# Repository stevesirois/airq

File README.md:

# AirQ

An indoor air-quality monitor built around an ESP32-C6 and a [Sensirion SEN66](https://sensirion.com/products/catalog/SEN66) sensor, running [ESPHome](https://esphome.io/) and reporting into [Home Assistant](https://www.home-assistant.io/) that will cost you around 125$ (CAD).

The SEN66 is an all-in-one environmental sensor that measures:

- **CO₂** concentration
- **PM1.0 / PM2.5 / PM4.0 / PM10** particulate matter
- **Temperature** and **relative humidity**
- **VOC index** and **NOx index**

These values are published to Home Assistant as individual sensor entities over Wi-Fi, using ESPHome's native API.

## Project structure

| Path                                 | Purpose                                                         |
| ------------------------------------ | --------------------------------------------------------------- |
| `airq.yaml`                          | ESPHome config for the **WaveShare ESP32-C6-Zero / mini** board |
| `airqx.yaml`                         | ESPHome config for the **Seeed Studio XIAO ESP32-C6** board     |
| `airQ (PCB)/`                        | KiCad carrier/breakout PCB (ESP32-C6 + SEN66 headers)           |
| `3D-Print/`                          | 3D-printable enclosure (body, cover, TPU gasket) + assembly     |
| `BOM.ods`, `BOM.csv`                 | Bill of materials spreadsheet                                   |
| `sensirion-datasheet-SEN6x-V1.0.pdf` | SEN66 sensor datasheet                                          |

## Hardware

- **MCU board:** either a
  - [WaveShare ESP32-C6-Zero / ESP32-C6 mini](https://www.espboards.dev/esp32/esp32-c6-zero-mini/) ([docs](https://docs.waveshare.com/ESP32-C6-Zero)), or a
  - [Seeed Studio XIAO ESP32C6](https://wiki.seeedstudio.com/xiao_esp32c6_getting_started/)
- **Sensor:** [Sensirion SEN66](https://sensirion.com/products/catalog/SEN66) (SEN6x family)
- **Carrier PCB:** a small breakout board (KiCad project in `airQ (PCB)/`) that hosts the ESP32-C6 board and the SEN66. Its headers are pin headers only — you solder the ESP32-C6 board and connect the sensor via its 6-pin cable. Manufacturable via [JLCPCB](https://jlcpcb.com/) using the files in `airQ (PCB)/production/`.
- **Enclosure:** 3D-printable body, cover, and TPU gasket (see `3D-Print/`), sized for the SEN66 with proper airflow openings (≥56 mm² inlet / ≥148 mm² outlet per Sensirion guidelines).

### Wiring (I²C)

| Board (config)                        | SCL    | SDA    |
| ------------------------------------- | ------ | ------ |
| WaveShare ESP32-C6-Zero (`airq.yaml`) | GPIO22 | GPIO21 |
| XIAO ESP32-C6 (`airqx.yaml`)          | GPIO23 | GPIO22 |

## Requirements

- **ESPHome** — see [esphome.io](https://esphome.io/) for installation. I suggest to use the executable version if you use Windows/MacOS or the AppImage if your are on Linux since this is the easiest way to use ESPHome

## Usage

1. Check the BOM.ods for all the required parts
2. Order your PCB from JLCPCB using the airQ.zip file that is ready for production
3. Depending of the controler used, short the 4 x 3 pins connectors accordingly on the PCB. The side mark "M" is for the Waveshare mini and the other side is for the Seeed XIAO (mark "X").
4. Print the enclosure
5. Configure and flash your controler using ESPHome. I put 2 yaml files that show the correct configuration for each board. The important part is the IO pin for the I²C interface vs the PCB board design
6. Assemble everything and hopefully it should work :-)

## Home Assistant dashboard for the sensor

To show the dashboard card (see picture in photo folder), install HACS (Home Assistant Community Store) and add the [Air Quality Card by KadenThomp36](https://github.com/KadenThomp36/Air-Quality-Card). The thresholds follow the WHO 2021 recommendations that this card also uses, so the recommendations on the device's display and the dashboard will stay consistent.

## Ordering / manufacturing

- **PCB:** upload the Gerber/drill files (the zip file) generated from `airQ (PCB)/production/airQ.zip` to [JLCPCB](https://jlcpcb.com/). The `production/` folder contains BOM and placement (CPL) exports for assembly.
- **Enclosure:** print the parts in `3D-Print/` (PLA body/cover, TPU for the gasket). See `3D-Print/README.md` for details.

## References

- [ESPHome](https://esphome.io/)
- [ESP32-C6-Zero — ESPBoards](https://www.espboards.dev/esp32/esp32-c6-zero-mini/)
- [ESP32-C6-Zero — WaveShare docs](https://docs.waveshare.com/ESP32-C6-Zero)
- [XIAO ESP32-C6 — ESPBoards](https://www.espboards.dev/esp32/xiao-esp32c6/)
- [XIAO ESP32-C6 — Seeed Studio wiki](https://wiki.seeedstudio.com/xiao_esp32c6_getting_started/)
- [Sensirion SEN66](https://sensirion.com/products/catalog/SEN66)
- [JLCPCB](https://jlcpcb.com/)

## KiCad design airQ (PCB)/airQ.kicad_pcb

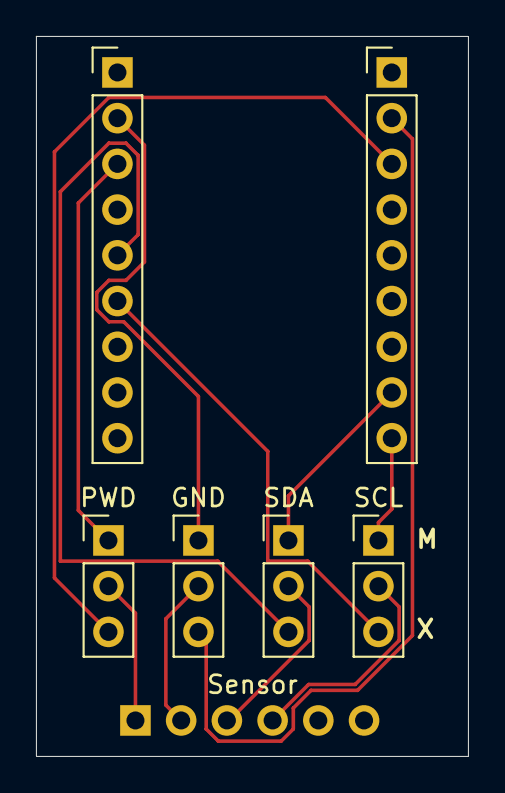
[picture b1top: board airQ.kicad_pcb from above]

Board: 2 copper layers, 24.0 x 40.0 mm, 7 parts (1 on the bottom side), 12 nets.

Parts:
GND: Conn_01x03_Pin; PinHeader_1x03_P2.54mm_Vertical
LeftRow1: Conn_01x09_Pin; PinHeader_1x09_P2.54mm_Vertical
PWD: Conn_01x03_Pin; PinHeader_1x03_P2.54mm_Vertical
RightRow1: Conn_01x09_Pin; PinHeader_1x09_P2.54mm_Vertical
SCL: Conn_01x03_Pin; PinHeader_1x03_P2.54mm_Vertical
SDA: Conn_01x03_Pin; PinHeader_1x03_P2.54mm_Vertical
Sensor: Conn_01x06_Pin; PinHeader_1x06_P2.54mm_Vertical

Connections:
unnamed: GND.1, LeftRow1.2
unnamed: GND.2, Sensor.2
unnamed: GND.3, RightRow1.2
unnamed: LeftRow1.3, PWD.1
unnamed: LeftRow1.5, SDA.3
unnamed: LeftRow1.6, SCL.3
unnamed: PWD.2, Sensor.1
unnamed: PWD.3, RightRow1.3
unnamed: RightRow1.8, SDA.1
unnamed: RightRow1.9, SCL.1
unnamed: SCL.2, Sensor.4
unnamed: SDA.2, Sensor.3

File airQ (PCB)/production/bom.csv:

Designator,Footprint,Quantity,Value,LCSC Part #
"GND, PWD, SCL, SDA",PinHeader_1x03_P2.54mm_Vertical,4,Conn_01x03_Pin,
"LEFTROW1, RIGHTROW1",PinHeader_1x09_P2.54mm_Vertical,2,Conn_01x09_Pin,
SENSOR,PinHeader_1x06_P2.54mm_Vertical,1,Conn_01x06_Pin,
